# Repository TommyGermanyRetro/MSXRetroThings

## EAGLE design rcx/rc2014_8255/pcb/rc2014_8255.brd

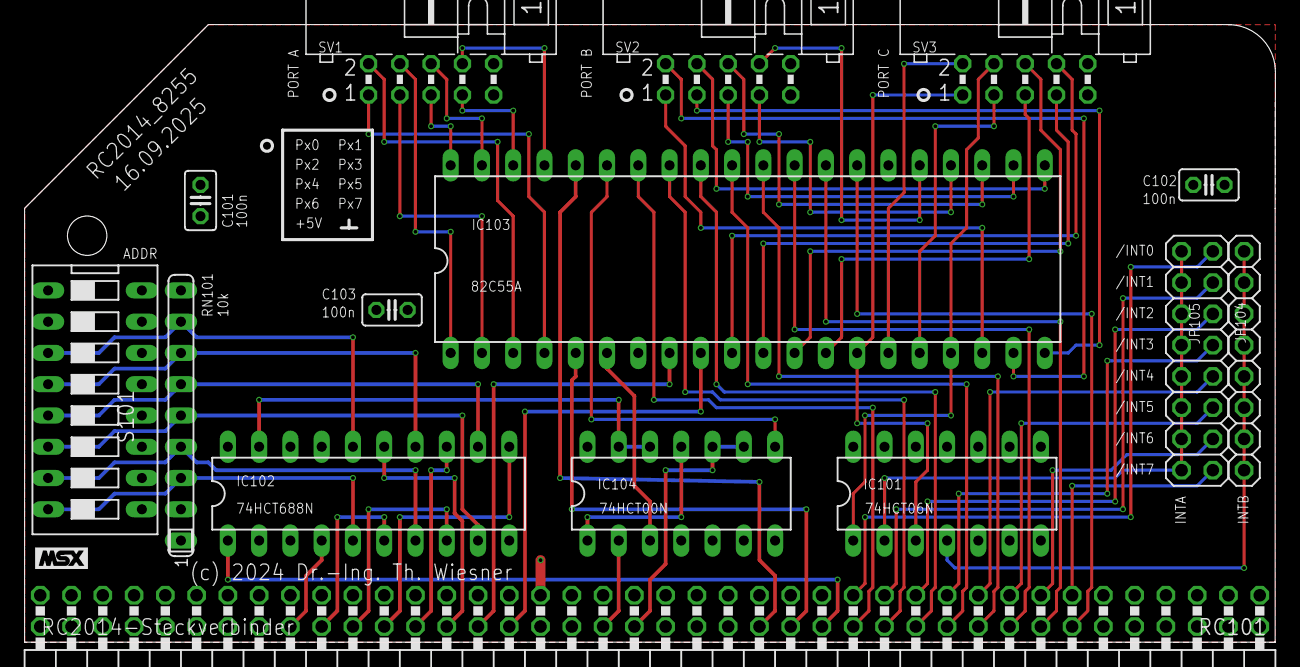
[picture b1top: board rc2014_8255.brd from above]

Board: 2 copper layers, 101.6 x 50.2 mm, 15 parts (0 on the bottom side), 67 nets.

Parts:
C101, C102, C103: 100n; C025-025X050
IC101: 74HCT06N; DIL14
IC102: 74HCT688N; DIL20
IC103: 82C55A; DIL40
IC104: 74HCT00N; DIL14
JP104: 1X08
JP105: 2X08
RC101: RC2014-Steckverbinder; RC2014-STECKER
RN101: 10k; SIL9
S101: ADDR; DS-08
SV1, SV2, SV3: ML10L

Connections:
+5V: C101.1, C102.1, C103.1, IC101.14, IC102.2, IC102.3, IC102.17, IC102.18, IC102.20, IC103.26, IC104.14, RC101.A18, RC101.B18, S101.9, S101.10, S101.11, S101.12, S101.13, S101.14, SV1.9, SV2.9, SV3.9
/CS: IC103.6, IC104.3
/INT0: JP105.2, RC101.B27
/INT1: JP105.4, RC101.B28
/INT2: JP105.6, RC101.B29
/INT3: JP105.8, RC101.B30
/INT4: JP105.10, RC101.B31
/INT5: JP105.12, RC101.B32
/INT6: JP105.14, RC101.B33
/INT7: JP105.16, RC101.B34
/INTA: IC101.2, JP105.1, JP105.3, JP105.5, JP105.7, JP105.9, JP105.11, JP105.13, JP105.15
/INTB: IC101.4, JP104.1, JP104.2, JP104.3, JP104.4, JP104.5, JP104.6, JP104.7, JP104.8
/IORQ: IC102.1, RC101.A26
/M1: IC104.2, RC101.A19
/PIOCS: IC102.19, IC104.12, IC104.13
/RD: IC103.5, RC101.A25
/RESET: IC104.9, IC104.10, RC101.A20
/WR: IC103.36, RC101.A24
A0: IC103.9, RC101.A16
A1: IC103.8, RC101.A15
A2: IC102.15, RC101.A14
A3: IC102.13, RC101.A13
A4: IC102.11, RC101.A12
A5: IC102.8, RC101.A11
A6: IC102.6, RC101.A10
A7: IC102.4, RC101.A9
D0: IC103.34, RC101.A27
D1: IC103.33, RC101.A28
D2: IC103.32, RC101.A29
D3: IC103.31, RC101.A30
D4: IC103.30, RC101.A31
D5: IC103.29, RC101.A32
D6: IC103.28, RC101.A33
D7: IC103.27, RC101.A34
GND: C101.2, C102.2, C103.2, IC101.5, IC101.7, IC101.9, IC101.11, IC101.13, IC102.10, IC103.7, IC104.4, IC104.5, IC104.7, RC101.A17, RC101.B17, RN101.1, SV1.10, SV2.10, SV3.10
unnamed: IC104.1, IC104.11
unnamed: IC102.16, RN101.8, S101.3
unnamed: IC102.14, RN101.7, S101.4
unnamed: IC102.12, RN101.6, S101.5
unnamed: IC102.9, RN101.5, S101.6
unnamed: IC102.7, RN101.4, S101.7
unnamed: IC102.5, RN101.3, S101.8
PA0: IC103.4, SV1.1
PA1: IC103.3, SV1.2
PA2: IC103.2, SV1.3
PA3: IC103.1, SV1.4
PA4: IC103.40, SV1.5
PA5: IC103.39, SV1.6
PA6: IC103.38, SV1.7
PA7: IC103.37, SV1.8
PB0: IC103.18, SV2.1
PB1: IC103.19, SV2.2
PB2: IC103.20, SV2.3
PB3: IC103.21, SV2.4
PB4: IC103.22, SV2.5
PB5: IC103.23, SV2.6
PB6: IC103.24, SV2.7
PB7: IC103.25, SV2.8
PC0: IC101.3, IC103.14, SV3.1
PC1: IC103.15, SV3.2
PC2: IC103.16, SV3.3
PC3: IC101.1, IC103.17, SV3.4
PC4: IC103.13, SV3.5
PC5: IC103.12, SV3.6
PC6: IC103.11, SV3.7
PC7: IC103.10, SV3.8
RESET: IC103.35, IC104.8

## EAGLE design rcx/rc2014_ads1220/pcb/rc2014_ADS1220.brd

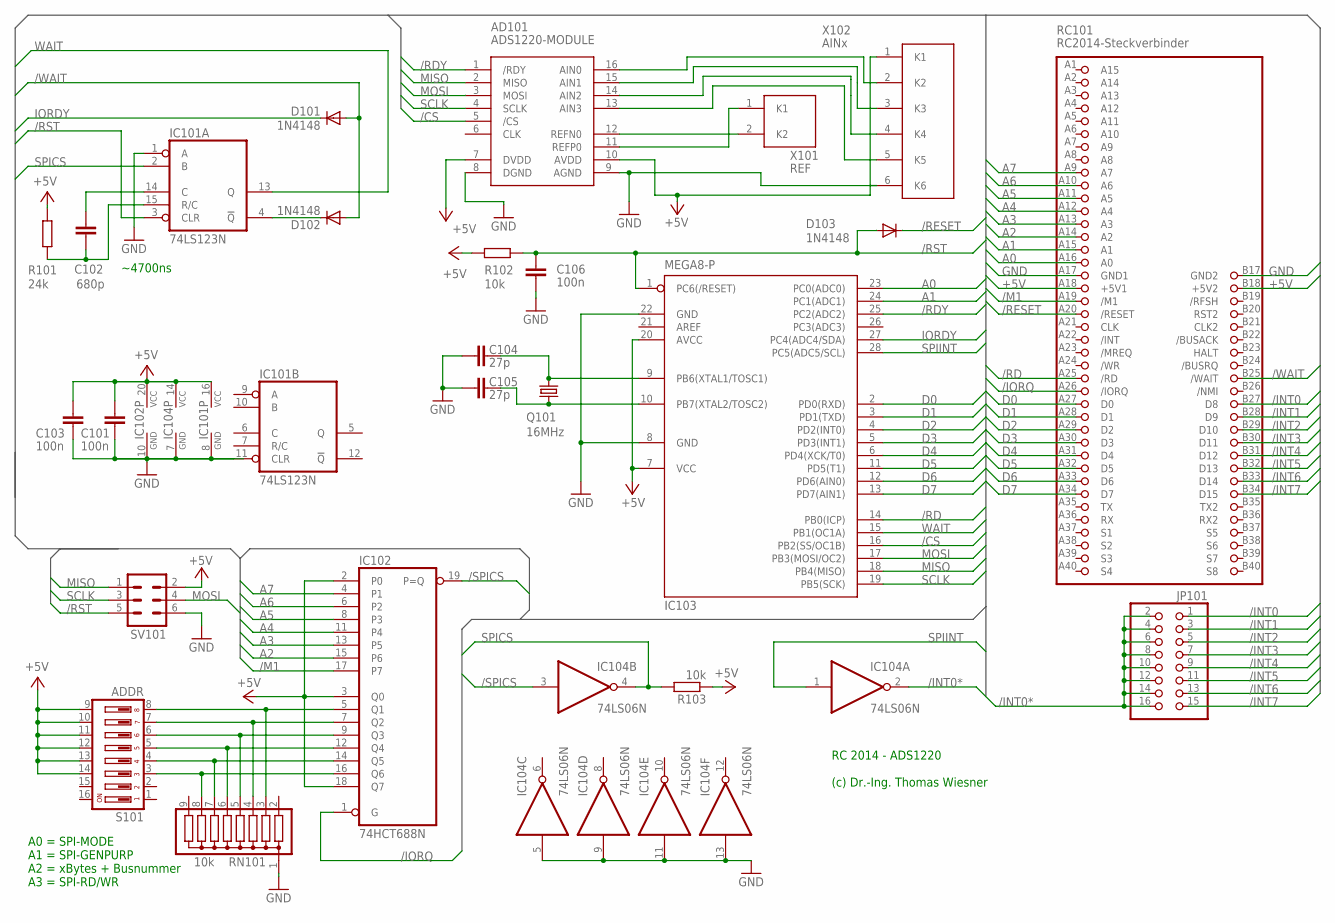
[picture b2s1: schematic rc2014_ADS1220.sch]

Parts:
AD101: ADS1220-MODULE; ADS1220-MOD
C101, C103, C106: 100n; C025-025X050
C102: 680p; C025-025X050
C104, C105: 27p; C025-025X050
D101, D102, D103: 1N4148; DO35-10
IC101: 74LS123N; DIL16
IC102: 74HCT688N; DIL20
IC103: MEGA8-P; DIL28-3
IC104: 74LS06N; DIL14
JP101: PINHD-2X8; 2X08
Q101: 16MHz; HC49U-V
R101: 24k; 0207/10
R102, R103: 10k; 0207/10
RC101: RC2014-Steckverbinder; RC2014-STECKER
RN101: 10k; SIL9
S101: ADDR; DS-08
SV101: ML6L
X101: REF; AKL182-2
X102: AINx; AKL182-6

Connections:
+5V: AD101.7 (DVDD), AD101.10 (AVDD), C101.2, C103.2, IC101.16 (VCC), IC102.2 (P0), IC102.3 (Q0), IC102.18 (Q7), IC102.20 (VCC), IC103.7 (VCC), IC103.20 (AVCC), IC104.14 (VCC), R101.1, R102.1, R103.1, RC101.A18 (+5V1), RC101.B18 (+5V2), S101.9, S101.10, S101.11, S101.12, S101.13, S101.14, SV101.2, X102.1 (K1)
/CS: AD101.5 (/CS), IC103.16 (PB2(SS/OC1B))
/INT0: JP101.1, RC101.B27 (D8)
/INT0*: IC104.2 (O), JP101.2, JP101.4, JP101.6, JP101.8, JP101.10, JP101.12, JP101.14, JP101.16
/INT1: JP101.3, RC101.B28 (D9)
/INT2: JP101.5, RC101.B29 (D10)
/INT3: JP101.7, RC101.B30 (D11)
/INT4: JP101.9, RC101.B31 (D12)
/INT5: JP101.11, RC101.B32 (D13)
/INT6: JP101.13, RC101.B33 (D14)
/INT7: JP101.15, RC101.B34 (D15)
/IORQ: IC102.1 (G), RC101.A26 (/IORQ)
/M1: IC102.17 (P7), RC101.A19 (/M1)
/RD: IC103.14 (PB0(ICP)), RC101.A25 (/RD)
/RDY: AD101.1 (/RDY), IC103.25 (PC2(ADC2))
/RESET: D103.C, RC101.A20 (/RESET)
/RST: C106.2, D103.A, IC101.3 (CLR), IC103.1 (PC6(/RESET)), R102.2, SV101.5
/SPICS: IC102.19 (P=Q), IC104.3 (I)
/WAIT: D101.A, D102.A, RC101.B25 (/WAIT)
A0: IC103.23 (PC0(ADC0)), RC101.A16 (A0)
A1: IC103.24 (PC1(ADC1)), RC101.A15 (A1)
A2: IC102.15 (P6), RC101.A14 (A2)
A3: IC102.13 (P5), RC101.A13 (A3)
A4: IC102.11 (P4), RC101.A12 (A4)
A5: IC102.8 (P3), RC101.A11 (A5)
A6: IC102.6 (P2), RC101.A10 (A6)
A7: IC102.4 (P1), RC101.A9 (A7)
D0: IC103.2 (PD0(RXD)), RC101.A27 (D0)
D1: IC103.3 (PD1(TXD)), RC101.A28 (D1)
D2: IC103.4 (PD2(INT0)), RC101.A29 (D2)
D3: IC103.5 (PD3(INT1)), RC101.A30 (D3)
D4: IC103.6 (PD4(XCK/T0)), RC101.A31 (D4)
D5: IC103.11 (PD5(T1)), RC101.A32 (D5)
D6: IC103.12 (PD6(AIN0)), RC101.A33 (D6)
D7: IC103.13 (PD7(AIN1)), RC101.A34 (D7)
GND: AD101.8 (DGND), AD101.9 (AGND), C101.1, C103.1, C104.2, C105.2, C106.1, IC101.1 (A), IC101.8 (GND), IC101.11 (CLR), IC102.10 (GND), IC103.8 (GND), IC103.22 (GND), IC104.5 (I), IC104.7 (GND), IC104.9 (I), IC104.11 (I), IC104.13 (I), RC101.A17 (GND1), RC101.B17 (GND2), RN101.1, SV101.6, X102.6 (K6)
IORDY: D101.C, IC103.27 (PC4(ADC4/SDA))
MISO: AD101.2 (MISO), IC103.18 (PB4(MISO)), SV101.1
MOSI: AD101.3 (MOSI), IC103.17 (PB3(MOSI/OC2)), SV101.4
unnamed: C102.1, IC101.15 (R/C), R101.2
unnamed: D102.C, IC101.4 (!Q)
unnamed: C105.1, IC103.10 (PB7(XTAL2/TOSC2)), Q101.1
unnamed: C102.2, IC101.14 (C)
unnamed: C104.1, IC103.9 (PB6(XTAL1/TOSC1)), Q101.2
unnamed: IC102.16 (Q6), RN101.8, S101.3
unnamed: IC102.14 (Q5), RN101.7, S101.4
unnamed: IC102.12 (Q4), RN101.6, S101.5
unnamed: IC102.9 (Q3), RN101.5, S101.6
unnamed: IC102.7 (Q2), RN101.4, S101.7
unnamed: IC102.5 (Q1), RN101.3, S101.8
unnamed: AD101.16 (AIN0), X102.2 (K2)
unnamed: AD101.15 (AIN1), X102.3 (K3)
unnamed: AD101.14 (AIN2), X102.4 (K4)
unnamed: AD101.13 (AIN3), X102.5 (K5)
unnamed: AD101.11 (REFP0), X101.1 (K1)
unnamed: AD101.12 (REFN0), X101.2 (K2)
SCLK: AD101.4 (SCLK), IC103.19 (PB5(SCK)), SV101.3
SPICS: IC101.2 (B), IC104.4 (O), R103.2
SPIINT: IC103.28 (PC5(ADC5/SCL)), IC104.1 (I)
WAIT: IC101.13 (Q), IC103.15 (PB1(OC1A))

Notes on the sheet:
RC 2014 - ADS1220 (c) Dr.-Ing. Thomas Wiesner
~4700ns
A0 = SPI-MODE A1 = SPI-GENPURP A2 = xBytes + Busnummer A3 = SPI-RD/WR

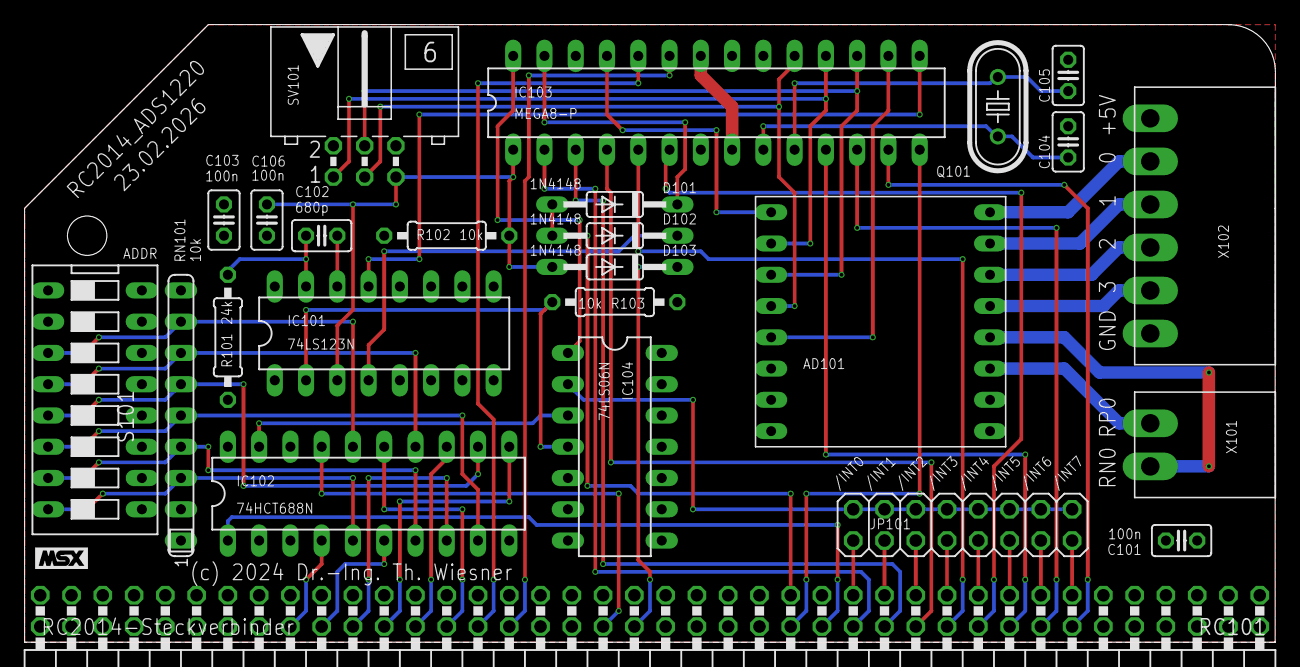
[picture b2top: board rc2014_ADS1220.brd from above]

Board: 2 copper layers, 101.6 x 50.2 mm, 25 parts (0 on the bottom side), 60 nets.

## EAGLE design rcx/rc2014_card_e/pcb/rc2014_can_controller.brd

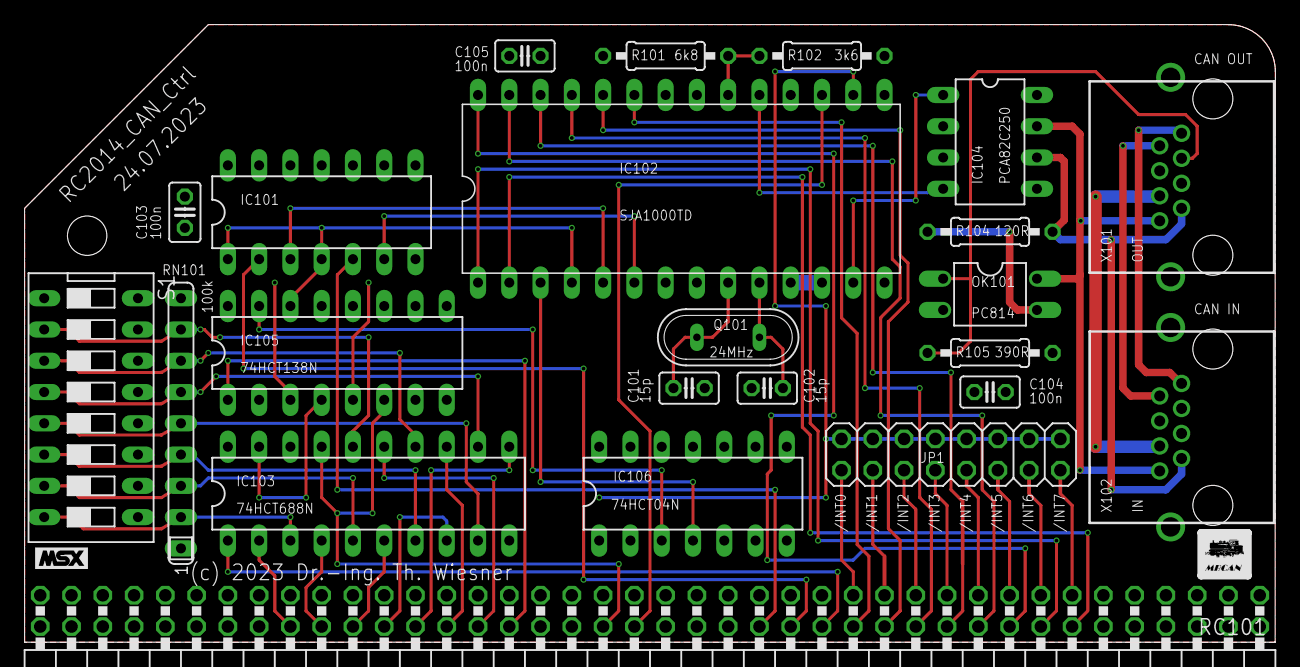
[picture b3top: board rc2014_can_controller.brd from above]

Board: 2 copper layers, 101.6 x 50.2 mm, 23 parts (0 on the bottom side), 57 nets.

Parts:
C101, C102: 15p; C025-025X050
C103, C104, C105: 100n; C025-025X050
IC101: 74HCT32N; DIL14
IC102: SJA1000TD; DIL28
IC103: 74HCT688N; DIL20
IC104: PCA82C250; DIL08
IC105: 74HCT138N; DIL16
IC106: 74HCT04N; DIL14
JP1: 2X08
OK101: PC814; DIL04
Q101: 24MHz; QS
R101: 6k8; 0207/10
R102: 3k6; 0207/10
R104: 120R; 0207/10
R105: 390R; 0207/10
RC101: RC2014-Steckverbinder; RC2014-STECKER
RN101: 100k; SIL9
S1: DS-08
X101: OUT; 0446200002
X102: IN; 0446200002

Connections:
+5V: C103.2, C104.2, C105.2, IC101.14, IC102.11, IC102.12, IC102.18, IC102.22, IC103.18, IC103.20, IC104.3, IC105.16, IC106.1, IC106.5, IC106.9, IC106.11, IC106.13, IC106.14, R101.1, R105.1, RC101.A18, RC101.B18, S1.9, S1.10, S1.11, S1.12, S1.13, S1.14, S1.15, S1.16
+18V: X101.6, X102.6
/ALE: IC105.15, IC106.3
/CS: IC101.1, IC101.4, IC102.4, IC105.14
/CSCAN: IC103.19, IC105.4
/INT0: JP1.16, RC101.B27
/INT1: JP1.14, RC101.B28
/INT2: JP1.12, RC101.B29
/INT3: JP1.10, RC101.B30
/INT4: JP1.8, RC101.B31
/INT5: JP1.6, RC101.B32
/INT6: JP1.4, RC101.B33
/INT7: JP1.2, RC101.B34
/INTCAN: IC102.16, JP1.1, JP1.3, JP1.5, JP1.7, JP1.9, JP1.11, JP1.13, JP1.15
/IORQ: IC103.1, RC101.A26
/M1: IC103.17, IC105.6, RC101.A19
/RD: IC101.2, RC101.A25
/RD#: IC101.3, IC102.5
/RESET: IC102.17, RC101.A20
/WR: IC101.5, RC101.A24
/WR#: IC101.6, IC102.6
A0: IC105.1, RC101.A16
A1: IC103.15, RC101.A15
A2: IC103.13, RC101.A14
A3: IC103.11, RC101.A13
A4: IC103.8, RC101.A12
A5: IC103.6, RC101.A11
A6: IC103.4, RC101.A10
A7: IC103.2, RC101.A9
ALE: IC102.3, IC106.4
CAN-H: IC104.7, OK101.4, X101.8, X102.8
CAN-L: IC104.6, R104.2, X101.7, X102.7
D0: IC102.23, RC101.A27
D1: IC102.24, RC101.A28
D2: IC102.25, RC101.A29
D3: IC102.26, RC101.A30
D4: IC102.27, RC101.A31
D5: IC102.28, RC101.A32
D6: IC102.1, RC101.A33
D7: IC102.2, RC101.A34
GND: C101.2, C102.2, C103.1, C104.1, C105.1, IC101.7, IC101.9, IC101.10, IC101.12, IC101.13, IC102.8, IC102.15, IC102.21, IC103.10, IC104.2, IC104.8, IC105.2, IC105.3, IC105.5, IC105.8, IC106.7, OK101.2, R102.1, RC101.A17, RC101.B17, RN101.1, X101.4, X101.5, X101.S@1, X101.S@2, X102.3, X102.4, X102.5, X102.S@1, X102.S@2
unnamed: OK101.1, R105.2, X101.3
unnamed: C101.1, IC102.9, Q101.2
unnamed: OK101.3, R104.1
unnamed: C102.1, IC102.10, Q101.1
unnamed: IC103.16, RN101.8, S1.2
unnamed: IC103.14, RN101.7, S1.3
unnamed: IC103.12, RN101.6, S1.4
unnamed: IC103.9, RN101.5, S1.5
unnamed: IC103.7, RN101.4, S1.6
unnamed: IC103.5, RN101.3, S1.7
unnamed: X101.2, X102.2
unnamed: X101.1, X102.1
unnamed: IC103.3, RN101.2, S1.8
unnamed: IC102.20, R101.2, R102.2
RX: IC102.19, IC104.4
TX: IC102.13, IC104.1

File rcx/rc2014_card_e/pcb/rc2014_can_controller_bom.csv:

Qty,Reference,Value,Package,Description
1,RC101,RC2014,RC2014-STECKER,"RC2014 enhanced bus connector, pin header 2 x 40, 2.54 mm, angled"
1,IC102,SJA1000,DIL28,"Stand-alone CAN controller (NXP SJA1000), DIL28"
1,IC104,PCA82C250,DIL08,CAN transceiver (NXP PCA82C250)
1,IC103,74HCT688N,DIL20,8-bit comparator: card address against the DIP switch
1,IC105,74HCT138N,DIL16,3-to-8 decoder
1,IC101,74HCT32N,DIL14,Quad OR
1,IC106,74HCT04N,DIL14,Hex inverter
1,OK101,PC814,DIL04,Optocoupler with AC input (Sharp PC814)
1,Q101,24MHz,QS,Crystal 24 MHz
2,"C101, C102",15p,C025-025X050,"Ceramic capacitor 15 pF, 2.5 mm pitch"
3,"C103, C104, C105",100n,C025-025X050,"Ceramic capacitor 100 nF, 2.5 mm pitch"
1,R101,6k8,0207/10,"Resistor 6k8, axial, 10 mm pitch"
1,R102,3k6,0207/10,"Resistor 3k6, axial, 10 mm pitch"
1,R104,120R,0207/10,"Resistor 120 Ohm, axial, 10 mm pitch: CAN termination"
1,R105,390R,0207/10,"Resistor 390 Ohm, axial, 10 mm pitch"
1,RN101,100k,SIL9,"Resistor network 8 x 100 kOhm, common pin, SIL9"
1,S1,ADDR,DS-08,DIP switch 8 positions: card address
2,"X101, X102",RJ45,0446200002,"RJ45 socket, shielded (Molex 44620-0002): CAN bus in and out"
1,JP1,2X08,2X08,"Pin header 2 x 8, 2.54 mm, with jumper: selects the interrupt line /INT0-/INT7 of the XIO PIC"

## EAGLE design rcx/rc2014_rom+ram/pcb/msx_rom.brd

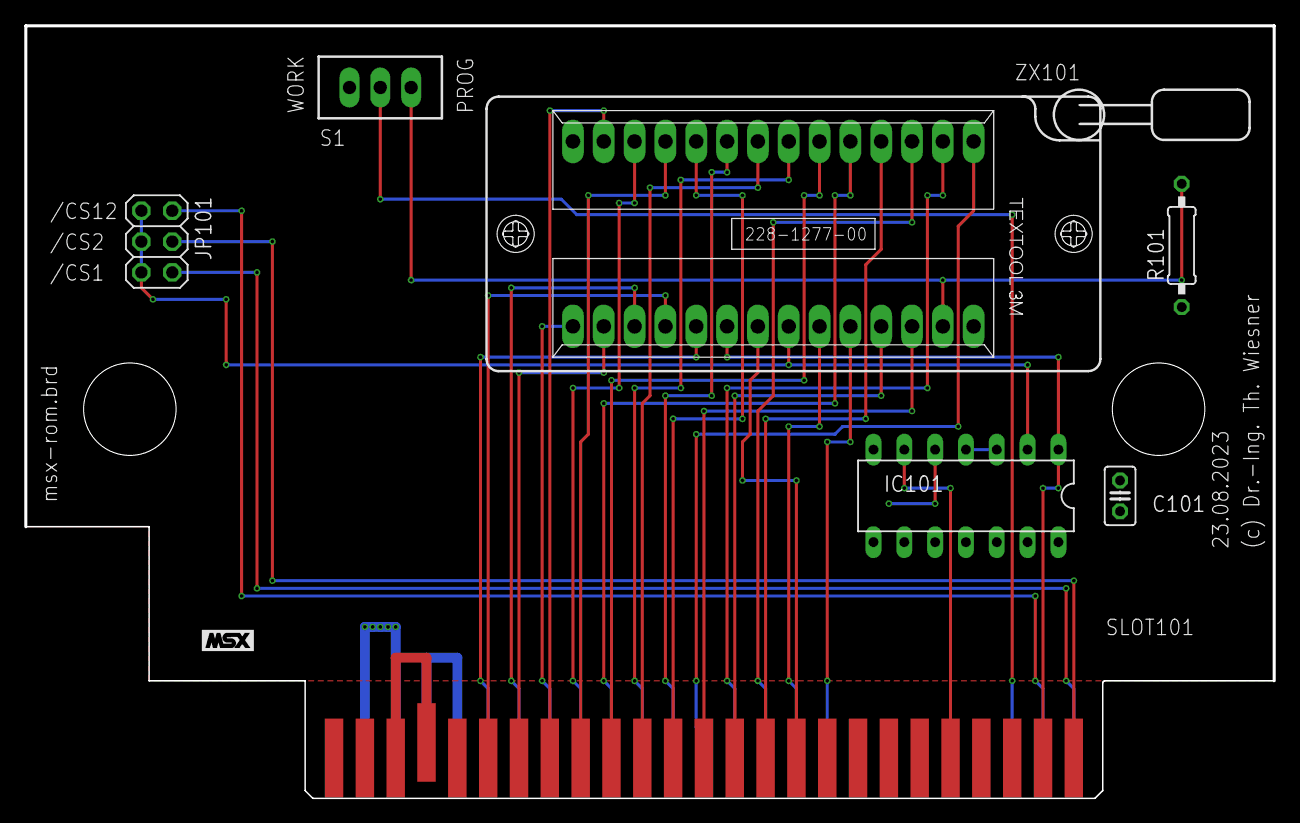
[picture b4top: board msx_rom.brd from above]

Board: 2 copper layers, 102.9 x 63.7 mm, 7 parts (0 on the bottom side), 35 nets.

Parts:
C101: 100n; C025-025X050
IC101: 74HCT32N; DIL14
JP101: 2X03
R101: 10k; 0207/10
S1: PROG; TL3XPO
SLOT101: MSXSLOT-CARD; MSXCARD
ZX101: 228-1277-00-0602J

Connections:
+5V: C101.2, IC101.14, R101.1, SLOT101.A23, SLOT101.A24, ZX101.28
/BUSDIR: IC101.6, SLOT101.B5
/CS1: JP101.6, SLOT101.A1
/CS2: JP101.4, SLOT101.B1
/CS12: JP101.2, SLOT101.A2
/OE: IC101.2, JP101.1, JP101.3, JP101.5, ZX101.22
/SLTSL: IC101.1, SLOT101.B2, ZX101.20
/WE: R101.2, S1.3, ZX101.27
/WEX: S1.2, SLOT101.A3
A0: SLOT101.B14, ZX101.10
A1: SLOT101.A14, ZX101.9
A2: SLOT101.B15, ZX101.8
A3: SLOT101.A15, ZX101.7
A4: SLOT101.B16, ZX101.6
A5: SLOT101.A16, ZX101.5
A6: SLOT101.B11, ZX101.4
A7: SLOT101.A11, ZX101.3
A8: SLOT101.B12, ZX101.25
A9: SLOT101.A9, ZX101.24
A10: SLOT101.B10, ZX101.21
A11: SLOT101.A10, ZX101.23
A12: SLOT101.A12, ZX101.2
A13: SLOT101.B13, ZX101.26
A14: SLOT101.A13, ZX101.1
D0: SLOT101.B17, ZX101.11
D1: SLOT101.A17, ZX101.12
D2: SLOT101.B18, ZX101.13
D3: SLOT101.A18, ZX101.15
D4: SLOT101.B19, ZX101.16
D5: SLOT101.A19, ZX101.17
D6: SLOT101.B20, ZX101.18
D7: SLOT101.A20, ZX101.19
GND: C101.1, IC101.7, IC101.9, IC101.10, IC101.12, IC101.13, SLOT101.A21, SLOT101.A22, ZX101.14
unnamed: IC101.3, IC101.4
unnamed: SLOT101.B22, SLOT101.B23

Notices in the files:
rcx/rc2014_8255/pcb/rc2014_8255.brd:
(c) 2024 Dr.-Ing. Th. Wiesner
rcx/rc2014_card_e/pcb/rc2014_can_controller.brd:
(c) 2023 Dr.-Ing. Th. Wiesner
